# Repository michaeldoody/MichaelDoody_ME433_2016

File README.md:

# MichaelDoody_ME433_2016

Michael Doody
April 4th, 2016

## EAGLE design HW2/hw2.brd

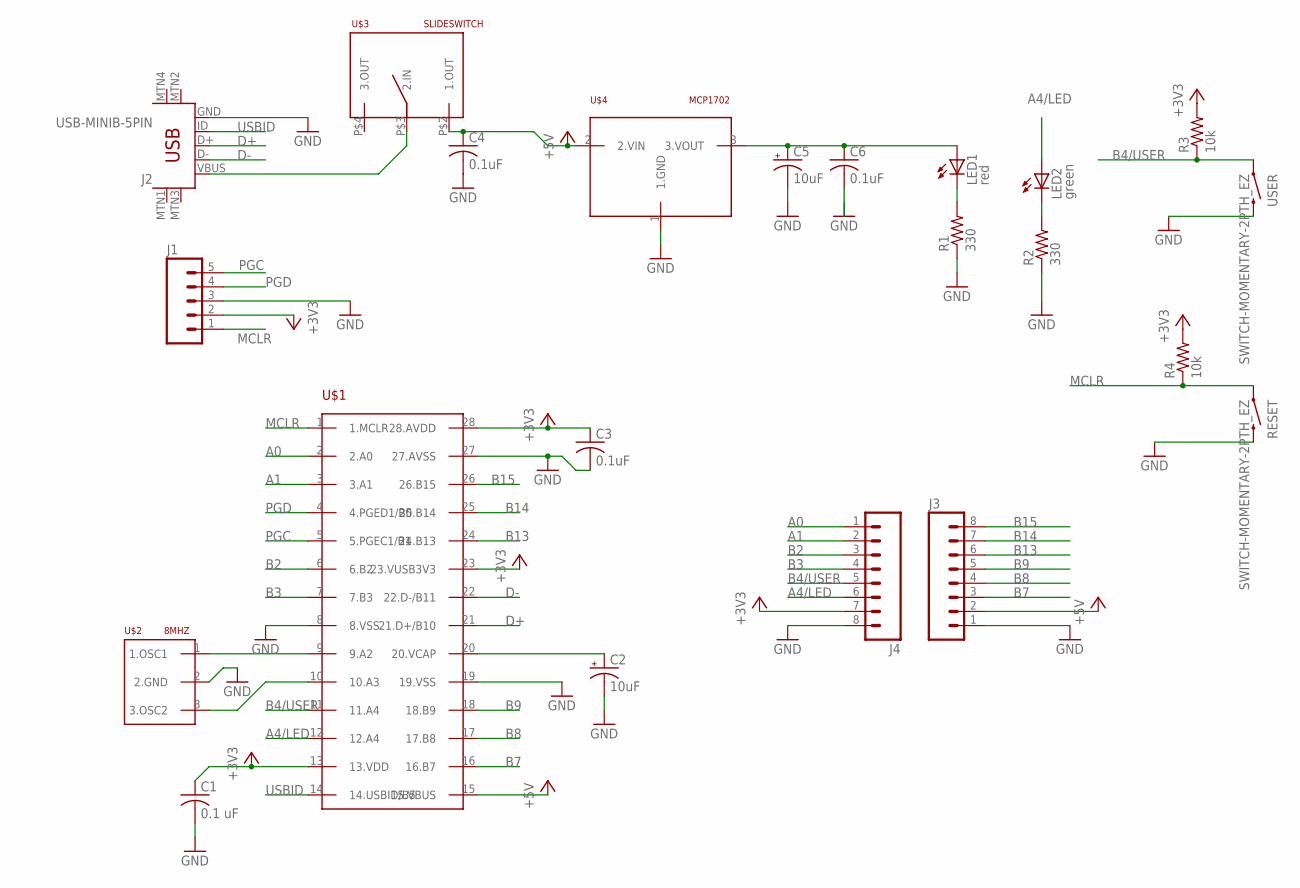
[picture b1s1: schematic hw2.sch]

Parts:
C1: 0.1 uF; C025-024X044
C2, C5: 10uF; 085CS_1AR
C3, C4, C6: 0.1uF; C025-024X044
J1: M05PTH; 1X05
J2: USB-MINIB-5PIN; USB-MINIB
J3, J4: M08; 1X08_ROUND
LED1: red; LED3MM
LED2: green; LED3MM
R1, R2: 330; 0207/10
R3, R4: 10k; 0207/10
RESET: SWITCH-MOMENTARY-2PTH_EZ; TACTILE-PTH-EZ
U$1: PIC32MX250F128B; DIL28-3
U$2: 8MHZ; RESONATOR-PTH
U$3: SLIDESWITCH
U$4: MCP1702; TO92
USER: SWITCH-MOMENTARY-2PTH_EZ; TACTILE-PTH-EZ

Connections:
+3V3: C1.1, C3.1, J1.2, J4.7, R3.2, R4.2, U$1.13 (13.VDD), U$1.23 (23.VUSB3V3), U$1.28 (28.AVDD)
+5V: C4.1, J3.2, U$1.15 (15.VBUS), U$3.P$2 (1.OUT), U$4.2 (2.VIN)
A0: J4.1, U$1.2 (2.A0)
A1: J4.2, U$1.3 (3.A1)
A4/LED: J4.6, LED2.A, U$1.12 (12.A4)
B2: J4.3, U$1.6 (6.B2)
B3: J4.4, U$1.7 (7.B3)
B4/USER: J4.5, R3.1, U$1.11 (11.A4), USER.1
B7: J3.3, U$1.16 (16.B7)
B8: J3.4, U$1.17 (17.B8)
B9: J3.5, U$1.18 (18.B9)
B13: J3.6, U$1.24 (24.B13)
B14: J3.7, U$1.25 (25.B14)
B15: J3.8, U$1.26 (26.B15)
D+: J2.D+, U$1.21 (21.D+/B10)
D-: J2.D-, U$1.22 (22.D-/B11)
GND: C1.2, C2.-, C3.2, C4.2, C5.-, J1.3, J2.GND, J3.1, J4.8, R1.1, R2.1, RESET.3 (2), U$1.8 (8.VSS), U$1.19 (19.VSS), U$1.27 (27.AVSS), U$2.2 (2.GND), U$4.1 (1.GND), USER.3 (2)
MCLR: J1.1, R4.1, RESET.1, U$1.1 (1.MCLR)
unnamed: U$1.9 (9.A2), U$2.1 (1.OSC1)
unnamed: U$1.10 (10.A3), U$2.3 (3.OSC2)
unnamed: J2.VBUS, U$3.P$3 (2.IN)
unnamed: LED1.K (C), R1.2
unnamed: C5.+, C6.1, LED1.A, U$4.3 (3.VOUT)
unnamed: LED2.K (C), R2.2
unnamed: C2.+, U$1.20 (20.VCAP)
PGC: J1.5, U$1.5 (5.PGEC1/B1)
PGD: J1.4, U$1.4 (4.PGED1/B0)
USBID: J2.ID, U$1.14 (14.USBID/B5)

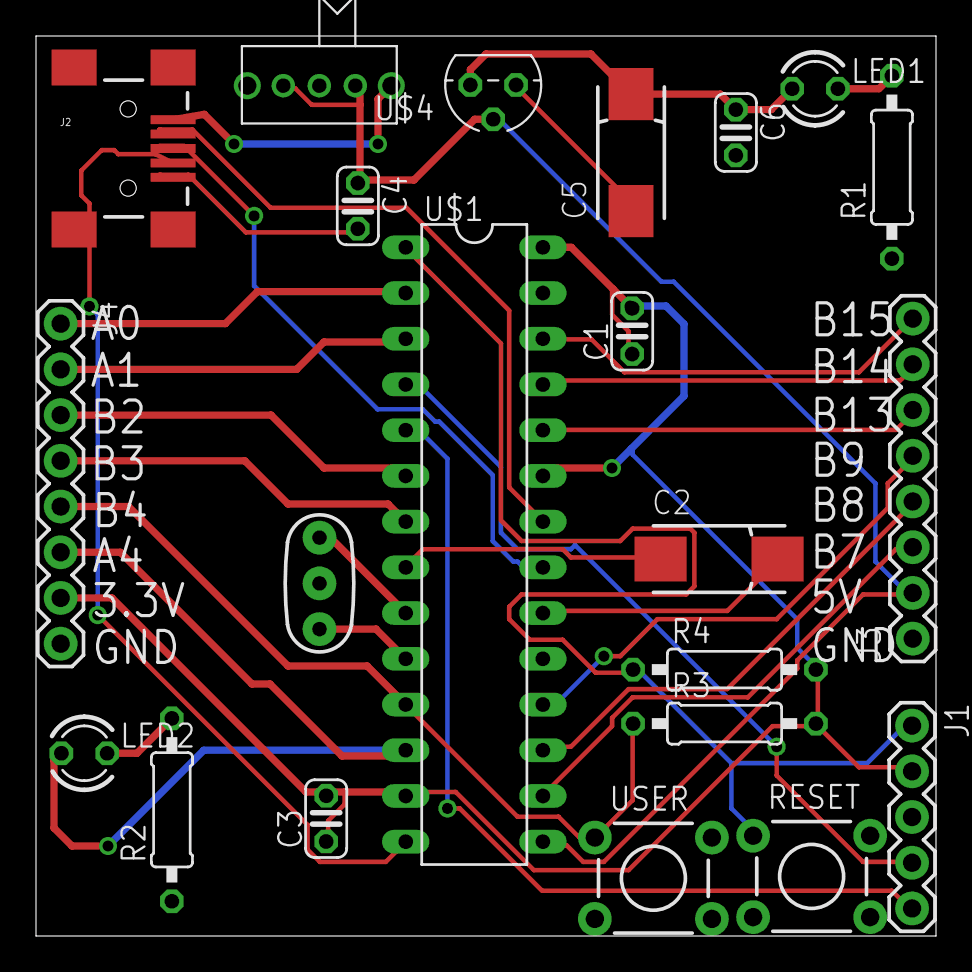
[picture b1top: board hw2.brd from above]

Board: 2 copper layers, 50.0 x 50.0 mm, 22 parts (0 on the bottom side), 28 nets.

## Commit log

2016-04-04 Create Poop
2016-04-04 Create circuit_diagram
2016-04-04 Added files via upload
2016-04-05 worked on HW1
2016-04-05 pragma commands
    filled out values for pragma commands
2016-04-11 compile test
    test
2016-04-11 test
    compile test
2016-04-11 green LED
    TRIS and LAT commands
2016-04-12 loop
    LED blink loop
2016-04-12 timer and pushbutton
    modified LED toggle
    added pushbutton code
    added comments
2016-04-12 Create hw2
2016-04-12 library
2016-04-14 Added files via upload
    Ready to be checked before order
2016-04-20 Create ...
2016-04-20 created file
2016-04-20 template
    spi example as a template
2016-04-25 hw4
    update
2016-04-25 pins and functions
    adapting example SPI code
2016-04-26 functions
    added I2C2 functions from repo
2016-05-16 Hello World
    beginning of HW9
2016-05-16 HW9
    adding in slider bar
2016-05-18 camera app
    copying and pasting code for robot camera app
2016-05-23 hw 10
    screenshot of CAD wheel
2016-05-24 hw 11
    screenshot of CAD, .dxf file, and photo of box
2016-06-01 hw 13
    android cdc
